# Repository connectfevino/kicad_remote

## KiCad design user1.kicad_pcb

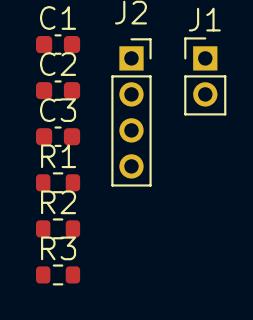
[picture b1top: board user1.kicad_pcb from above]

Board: 2 copper layers, 8 parts (0 on the bottom side), 3 nets, no tracks yet.

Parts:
C1, C2, C3: 0.1uF; C_0603_1608Metric
J1: BERG STRIP; PinHeader_1x02_P2.00mm_Vertical
J2: BERG STRIP; PinSocket_1x04_P2.00mm_Vertical
R1, R2, R3: 4K7; R_0603_1608Metric

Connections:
ESP_RST: C2.1, R1.2
GND: C1.2, C2.2, C3.2, J1.1, J2.4
VCC_3V: C1.1, C3.1, J2.1, R1.1, R2.1, R3.1

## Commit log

2026-02-05 init
2026-02-05 working design notes and add task feature
2026-02-05 workign cross broping, noted kanban board satisfactory ly
2026-02-05 multi user chat feature added
2026-02-05 Update 15:21
2026-02-05 Update 15:50
2026-02-05 annoted
2026-02-05 changes in the code andflush
2026-02-05 working , git with publichs a,
2026-02-05 wokring al
2026-02-05 init working
